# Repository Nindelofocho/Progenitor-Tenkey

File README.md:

# Progenitor Tenkey
 A 96 key custom made keyboard project

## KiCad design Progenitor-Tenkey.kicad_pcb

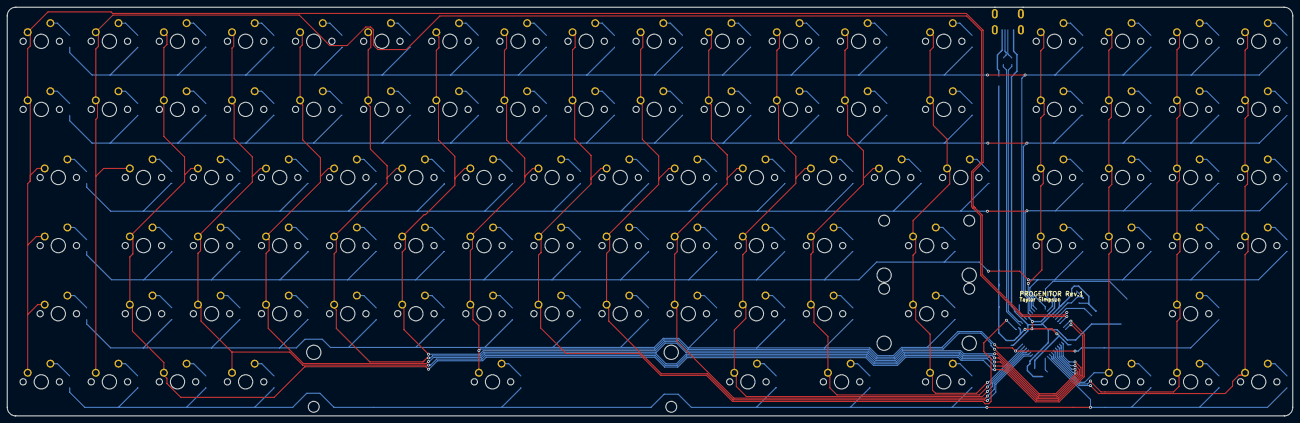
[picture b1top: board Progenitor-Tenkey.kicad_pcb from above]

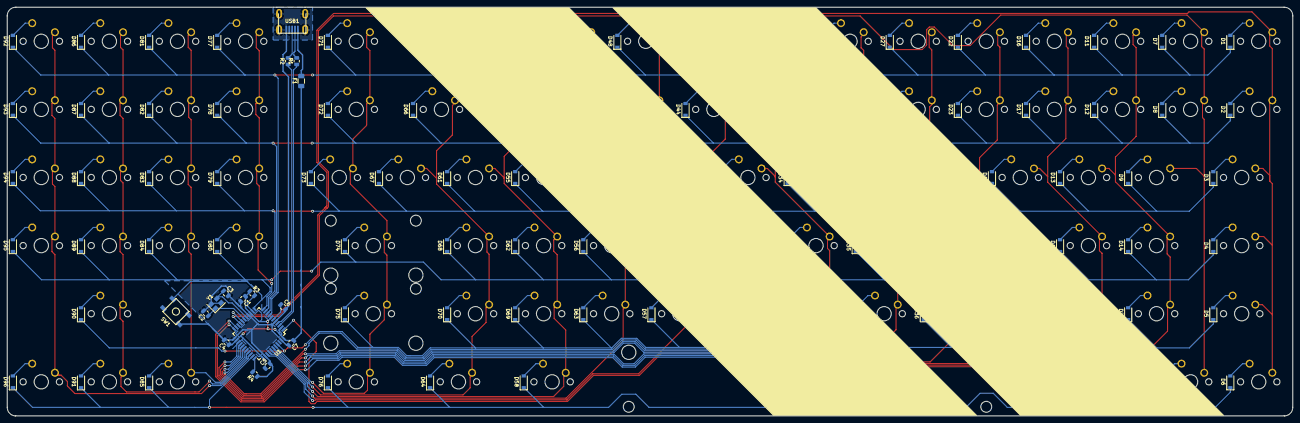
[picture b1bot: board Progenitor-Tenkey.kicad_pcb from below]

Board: 2 copper layers, 359.6 x 114.3 mm, 208 parts (112 on the bottom side), 132 nets.

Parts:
C1, C4, C5: 0.1uF; C_0805_2012Metric
C2, C3: 22pF; C_0805_2012Metric
C6: 1uF; C_0805_2012Metric
C7: 10uF; C_0805_2012Metric
D1, D2, D3, D4, D5, D6, D7, D8, D9, D10, D11, D12, D13, D14, D15, D16, D17, D18, D19, D20, D21, D22, D23, D24, D25, D26, D27, D28, D29, D30, D31, D32, D33, D34, D35, D36, D37, D38, D39, D40, D41, D42, D43, D44, D45, D46, D47, D48, D49, D50, D51, D52, D53, D54, D55, D56, D57, D58, D59, D60, D61, D62, D63, D64, D65, D66, D67, D68, D69, D70, D71, D72, D73, D74, D75, D76, D77, D78, D79, D80, D81, D82, D83, D84, D85, D86, D87, D88, D89, D90, D91, D92, D93, D94, D95, D96: D_Small; D_SOD-123
F1: Polyfuse_Small; Fuse_1206_3216Metric
MX-0, MX-1, MX-2, MX-3, MX-4, MX-5, MX-6, MX-7, MX-8, MX-9: MX-NoLED; MXOnly-1U-NoLED
MX-A1: MX-NoLED; MXOnly-1U-NoLED
MX-B1: MX-NoLED; MXOnly-1U-NoLED
MX-BAC1: MX-NoLED; MXOnly-1.5U-NoLED
MX-C1: MX-NoLED; MXOnly-1U-NoLED
MX-CAP1: MX-NoLED; MXOnly-1.5U-NoLED
MX-COL1: MX-NoLED; MXOnly-1U-NoLED
MX-CUR1: MX-NoLED; MXOnly-1U-NoLED
MX-D1: MX-NoLED; MXOnly-1U-NoLED
MX-DAR1: MX-NoLED; MXOnly-1U-NoLED
MX-DAS1: MX-NoLED; MXOnly-1U-NoLED
MX-DEL1: MX-NoLED; MXOnly-1.5U-NoLED
MX-E1: MX-NoLED; MXOnly-1U-NoLED
MX-ENT1: MX-NoLED; MXOnly-2U-NoLED
MX-ESC1: MX-NoLED; MXOnly-1U-NoLED
MX-F1, MX-F2, MX-F3, MX-F4, MX-F5, MX-F6, MX-F7, MX-F8, MX-F9, MX-F10, MX-F11, MX-F12, MX-F13: MX-NoLED; MXOnly-1U-NoLED
MX-FSL1: MX-NoLED; MXOnly-1U-NoLED
MX-G1: MX-NoLED; MXOnly-1U-NoLED
MX-GRE1: MX-NoLED; MXOnly-1U-NoLED
MX-H1: MX-NoLED; MXOnly-1U-NoLED
MX-I1: MX-NoLED; MXOnly-1U-NoLED
MX-J1: MX-NoLED; MXOnly-1U-NoLED
MX-K1: MX-NoLED; MXOnly-1U-NoLED
MX-L1: MX-NoLED; MXOnly-1U-NoLED
MX-LAL1: MX-NoLED; MXOnly-1U-NoLED
MX-LAR1: MX-NoLED; MXOnly-1U-NoLED
MX-LBR1: MX-NoLED; MXOnly-1U-NoLED
MX-LCT1: MX-NoLED; MXOnly-1U-NoLED
MX-LES1: MX-NoLED; MXOnly-1U-NoLED
MX-LFN1: MX-NoLED; MXOnly-1U-NoLED
MX-LSH1: MX-NoLED; MXOnly-1.5U-NoLED
MX-M1: MX-NoLED; MXOnly-1U-NoLED
MX-N0, MX-N1, MX-N2, MX-N3, MX-N4, MX-N5, MX-N6, MX-N7, MX-N8, MX-N9, MX-N10: MX-NoLED; MXOnly-1U-NoLED
MX-NAS1: MX-NoLED; MXOnly-1U-NoLED
MX-NDA1: MX-NoLED; MXOnly-1U-NoLED
MX-NDE1: MX-NoLED; MXOnly-1U-NoLED
MX-NPL1: MX-NoLED; MXOnly-1U-NoLED
MX-NSL1: MX-NoLED; MXOnly-1U-NoLED
MX-NUM1: MX-NoLED; MXOnly-1U-NoLED
MX-O1: MX-NoLED; MXOnly-1U-NoLED
MX-P1: MX-NoLED; MXOnly-1U-NoLED
MX-PLU1: MX-NoLED; MXOnly-1U-NoLED
MX-PRT1: MX-NoLED; MXOnly-1.5U-NoLED
MX-Q1: MX-NoLED; MXOnly-1U-NoLED
MX-QUE1: MX-NoLED; MXOnly-1U-NoLED
MX-QUO1: MX-NoLED; MXOnly-1U-NoLED
MX-R1: MX-NoLED; MXOnly-1U-NoLED
MX-RAL1: MX-NoLED; MXOnly-1.25U-NoLED
MX-RAR1: MX-NoLED; MXOnly-1U-NoLED
MX-RBR1: MX-NoLED; MXOnly-1U-NoLED
MX-RCT1: MX-NoLED; MXOnly-1.5U-NoLED
MX-RSH1: MX-NoLED; MXOnly-2U-NoLED
MX-S1: MX-NoLED; MXOnly-1U-NoLED
MX-SPA1: MX-NoLED; MXOnly-6.25U-ReversedStabilizers-NoLED
MX-T1: MX-NoLED; MXOnly-1U-NoLED
MX-TAB1: MX-NoLED; MXOnly-1.5U-NoLED
MX-TIL1: MX-NoLED; MXOnly-1U-NoLED
MX-U1: MX-NoLED; MXOnly-1U-NoLED
MX-UAR1: MX-NoLED; MXOnly-1U-NoLED
MX-V1: MX-NoLED; MXOnly-1U-NoLED
MX-W1: MX-NoLED; MXOnly-1U-NoLED
MX-WIN1: MX-NoLED; MXOnly-1U-NoLED
MX-X1: MX-NoLED; MXOnly-1U-NoLED
MX-Y1: MX-NoLED; MXOnly-1U-NoLED
MX-Z1: MX-NoLED; MXOnly-1U-NoLED
R1, R2: R_Small; R_0805_2012Metric
R3, R4: 10k; R_0805_2012Metric
SW1: SW_Push; SKQG-1155865
U1: ATmega32U4-AU; TQFP-44_10x10mm_P0.8mm
USB1: Molex-0548190589
Y1: 16MHz; Crystal_SMD_3225-4Pin_3.2x2.5mm

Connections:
+5V: C1.1, C4.1, C5.1, C7.1, F1.1, R3.1, U1.2, U1.7, U1.14, U1.24, U1.34, U1.44
COL00: MX-CAP1.1, MX-ESC1.1, MX-LCT1.1, MX-LSH1.1, MX-TAB1.1, MX-TIL1.1, U1.18
COL01: MX-1.1, MX-F1.1, MX-LFN1.1, MX-Q1.1, U1.19
COL02: MX-2.1, MX-A1.1, MX-F2.1, MX-W1.1, MX-WIN1.1, MX-Z1.1, U1.21
COL03: MX-3.1, MX-E1.1, MX-F3.1, MX-LAL1.1, MX-S1.1, MX-X1.1, U1.22
COL04: MX-4.1, MX-C1.1, MX-D1.1, MX-F4.1, MX-R1.1, U1.25
COL05: MX-5.1, MX-F5.1, MX-F13.1, MX-T1.1, MX-V1.1, U1.26
COL06: MX-6.1, MX-B1.1, MX-F6.1, MX-G1.1, MX-Y1.1, U1.27
COL07: MX-7.1, MX-F7.1, MX-H1.1, MX-N10.1, MX-SPA1.1, MX-U1.1, U1.28
COL08: MX-8.1, MX-F8.1, MX-I1.1, MX-J1.1, MX-M1.1, U1.1
COL09: MX-9.1, MX-F9.1, MX-K1.1, MX-LES1.1, MX-O1.1, U1.36
COL10: MX-0.1, MX-F10.1, MX-GRE1.1, MX-L1.1, MX-P1.1, U1.37
COL11: MX-COL1.1, MX-DAS1.1, MX-F11.1, MX-LBR1.1, MX-QUE1.1, MX-RAL1.1, U1.38
COL12: MX-CUR1.1, MX-F12.1, MX-PLU1.1, MX-PRT1.1, MX-QUO1.1, MX-RBR1.1, U1.39
COL13: MX-BAC1.1, MX-DEL1.1, MX-ENT1.1, MX-FSL1.1, MX-RCT1.1, MX-RSH1.1, U1.40
COL14: MX-N1.1, MX-N4.1, MX-N7.1, MX-NUM1.1, U1.11
COL15: MX-LAR1.1, MX-N0.1, MX-N2.1, MX-N5.1, MX-N8.1, U1.29
COL16: MX-DAR1.1, MX-N3.1, MX-N6.1, MX-N9.1, MX-NDE1.1, MX-UAR1.1, U1.30
COL17: MX-NAS1.1, MX-NDA1.1, MX-NPL1.1, MX-NSL1.1, MX-RAR1.1, U1.31
D+: R2.2, USB1.3
D-: R1.2, USB1.4
GND: C1.2, C2.2, C3.2, C4.2, C5.2, C6.2, C7.2, R4.1, SW1.1, U1.5, U1.15, U1.23, U1.35, U1.43, USB1.1, USB1.6, Y1.2, Y1.4
unnamed: C2.1, U1.17, Y1.1
unnamed: C3.1, U1.16, Y1.3
unnamed: C6.1, U1.6
unnamed: D1.2, MX-ESC1.2
unnamed: D2.2, MX-TIL1.2
unnamed: D3.2, MX-TAB1.2
unnamed: D4.2, MX-CAP1.2
unnamed: D5.2, MX-LSH1.2
unnamed: D6.2, MX-LCT1.2
unnamed: D7.2, MX-F1.2
unnamed: D8.2, MX-1.2
unnamed: D9.2, MX-Q1.2
unnamed: D10.2, MX-LFN1.2
unnamed: D11.2, MX-F2.2
unnamed: D12.2, MX-2.2
unnamed: D13.2, MX-W1.2
unnamed: D14.2, MX-A1.2
unnamed: D15.2, MX-WIN1.2
unnamed: D16.2, MX-F3.2
unnamed: D17.2, MX-3.2
unnamed: D18.2, MX-E1.2
unnamed: D19.2, MX-S1.2
unnamed: D20.2, MX-Z1.2
unnamed: D21.2, MX-LAL1.2
unnamed: D22.2, MX-F4.2
unnamed: D23.2, MX-4.2
unnamed: D24.2, MX-R1.2
unnamed: D25.2, MX-D1.2
unnamed: D26.2, MX-X1.2
unnamed: D27.2, MX-F5.2
unnamed: D28.2, MX-5.2
unnamed: D29.2, MX-T1.2
unnamed: D30.2, MX-F13.2
unnamed: D31.2, MX-C1.2
unnamed: D32.2, MX-F6.2
unnamed: D33.2, MX-6.2
unnamed: D34.2, MX-Y1.2
unnamed: D35.2, MX-G1.2
unnamed: D36.2, MX-V1.2
unnamed: D37.2, MX-F7.2
unnamed: D38.2, MX-7.2
unnamed: D39.2, MX-U1.2
unnamed: D40.2, MX-H1.2
unnamed: D41.2, MX-B1.2
unnamed: D42.2, MX-SPA1.2
unnamed: D43.2, MX-F8.2
unnamed: D44.2, MX-8.2
unnamed: D45.2, MX-I1.2
unnamed: D46.2, MX-J1.2
unnamed: D47.2, MX-N10.2
unnamed: D48.2, MX-F9.2
unnamed: D49.2, MX-9.2
unnamed: D50.2, MX-O1.2
unnamed: D51.2, MX-K1.2
unnamed: D52.2, MX-M1.2
unnamed: D53.2, MX-F10.2
unnamed: D54.2, MX-0.2
unnamed: D55.2, MX-P1.2
unnamed: D56.2, MX-L1.2
unnamed: D57.2, MX-LES1.2
unnamed: D58.2, MX-RAL1.2
unnamed: D59.2, MX-F11.2
unnamed: D60.2, MX-DAS1.2
unnamed: D61.2, MX-LBR1.2
unnamed: D62.2, MX-COL1.2
unnamed: D63.2, MX-GRE1.2
unnamed: D64.2, MX-PRT1.2
unnamed: D65.2, MX-F12.2
unnamed: D66.2, MX-PLU1.2
unnamed: D67.2, MX-RBR1.2
unnamed: D68.2, MX-QUO1.2
unnamed: D69.2, MX-QUE1.2
unnamed: D70.2, MX-CUR1.2
unnamed: D71.2, MX-DEL1.2
unnamed: D72.2, MX-BAC1.2
unnamed: D73.2, MX-FSL1.2
unnamed: D74.2, MX-ENT1.2
unnamed: D75.2, MX-RSH1.2
unnamed: D76.2, MX-RCT1.2
unnamed: D77.2, MX-N7.2
unnamed: D78.2, MX-N4.2
unnamed: D79.2, MX-N1.2
unnamed: D80.2, MX-NUM1.2
unnamed: D81.2, MX-N8.2
unnamed: D82.2, MX-N5.2
unnamed: D83.2, MX-N2.2
unnamed: D84.2, MX-N0.2
unnamed: D85.2, MX-LAR1.2
unnamed: D86.2, MX-N9.2
unnamed: D87.2, MX-N6.2
unnamed: D88.2, MX-N3.2
unnamed: D89.2, MX-NDE1.2
unnamed: D90.2, MX-UAR1.2
unnamed: D91.2, MX-DAR1.2
unnamed: D92.2, MX-NSL1.2
unnamed: D93.2, MX-NAS1.2
unnamed: D94.2, MX-NDA1.2
unnamed: D95.2, MX-NPL1.2
unnamed: D96.2, MX-RAR1.2
unnamed: R1.1, U1.3
unnamed: R2.1, U1.4
unnamed: R3.2, SW1.2, U1.13
unnamed: R4.2, U1.33
ROW00: D1.1, D7.1, D11.1, D16.1, D22.1, D27.1, D32.1, D37.1, D43.1, D48.1, D53.1, D59.1, D65.1, D71.1, D77.1, D81.1, D86.1, D92.1, U1.8
ROW01: D2.1, D8.1, D12.1, D17.1, D23.1, D28.1, D33.1, D38.1, D44.1, D49.1, D54.1, D60.1, D66.1, D72.1, D78.1, D82.1, D87.1, D93.1, U1.9
ROW02: D3.1, D9.1, D13.1, D18.1, D24.1, D29.1, D34.1, D39.1, D45.1, D50.1, D55.1, D61.1, D67.1, D73.1, D79.1, D83.1, D88.1, D94.1, U1.10
ROW03: D4.1, D14.1, D19.1, D25.1, D30.1, D35.1, D40.1, D46.1, D51.1, D56.1, D62.1, D68.1, D74.1, D80.1, D84.1, D89.1, D95.1, U1.12
ROW04: D5.1, D20.1, D26.1, D31.1, D36.1, D41.1, D47.1, D52.1, D57.1, D63.1, D69.1, D70.1, D75.1, D90.1, U1.41
ROW05: D6.1, D10.1, D15.1, D21.1, D42.1, D58.1, D64.1, D76.1, D85.1, D91.1, D96.1, U1.32
VCC: F1.2, USB1.5

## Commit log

2021-04-09 Initialize Project
2021-04-09 Add submodules
2021-04-09 Create fp-info-cache
2021-04-09 Add Footprint Libraries
2021-04-10 Added components
2021-04-10 Assigned Footprints
2021-04-11 Designed PCB Rev.1
2021-04-11 Small Tweaks
2021-04-11 Aesthetic Tweak
2021-04-11 Generated Gerber
2021-04-11 More tweaks, regenerated Gerber
2021-04-11 Prettyfied Files, Prettyfied Board a little, Added pretty renders
2021-04-11 Added Layouts
2021-04-12 Tweaks
2021-04-13 Board Rev.2
2021-04-13 Fixed Bugs
2021-04-13 Fixed Errors
